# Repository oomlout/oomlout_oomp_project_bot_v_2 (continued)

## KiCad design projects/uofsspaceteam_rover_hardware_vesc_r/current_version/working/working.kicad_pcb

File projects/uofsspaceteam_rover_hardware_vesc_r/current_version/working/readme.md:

# rover_hardware
 
## summary 
* id: uofsspaceteam_rover_hardware_vesc_r
* user: uofsspaceteam
* name: rover_hardware
* board: vesc_r
* repo: https://github.com/UofSSpaceTeam/rover-hardware
* src_file_repo_kicad_pcb: Projects/Communication/VESC-R/VESC-R.kicad_pcb
* src_file_repo_kicad_pcb_link: https://github.com/UofSSpaceTeam/rover-hardware/tree/master/Projects/Communication/VESC-R/VESC-R.kicad_pcb
* src_file_repo_kicad_sch: Projects/Communication/VESC-R/CAN.kicad_sch
* src_file_repo_kicad_sch_link: https://github.com/UofSSpaceTeam/rover-hardware/tree/master/Projects/Communication/VESC-R/CAN.kicad_sch
* src_file_repo_brd: Projects/Communication/KiCad_USB/modified_eagle_files/RH025.1.brd
* src_file_repo_brd_link: https://github.com/UofSSpaceTeam/rover-hardware/tree/master/Projects/Communication/KiCad_USB/modified_eagle_files/RH025.1.brd
* src_file_repo_sch: Projects/Communication/KiCad_USB/RH025.1.sch
* src_file_repo_sch_link: https://github.com/UofSSpaceTeam/rover-hardware/tree/master/Projects/Communication/KiCad_USB/RH025.1.sch
* full details link: https://github.com/oomlout/oomlout_oomp_project_bot_v_2/tree/main/projects/uofsspaceteam_rover_hardware_vesc_r/current_version/working

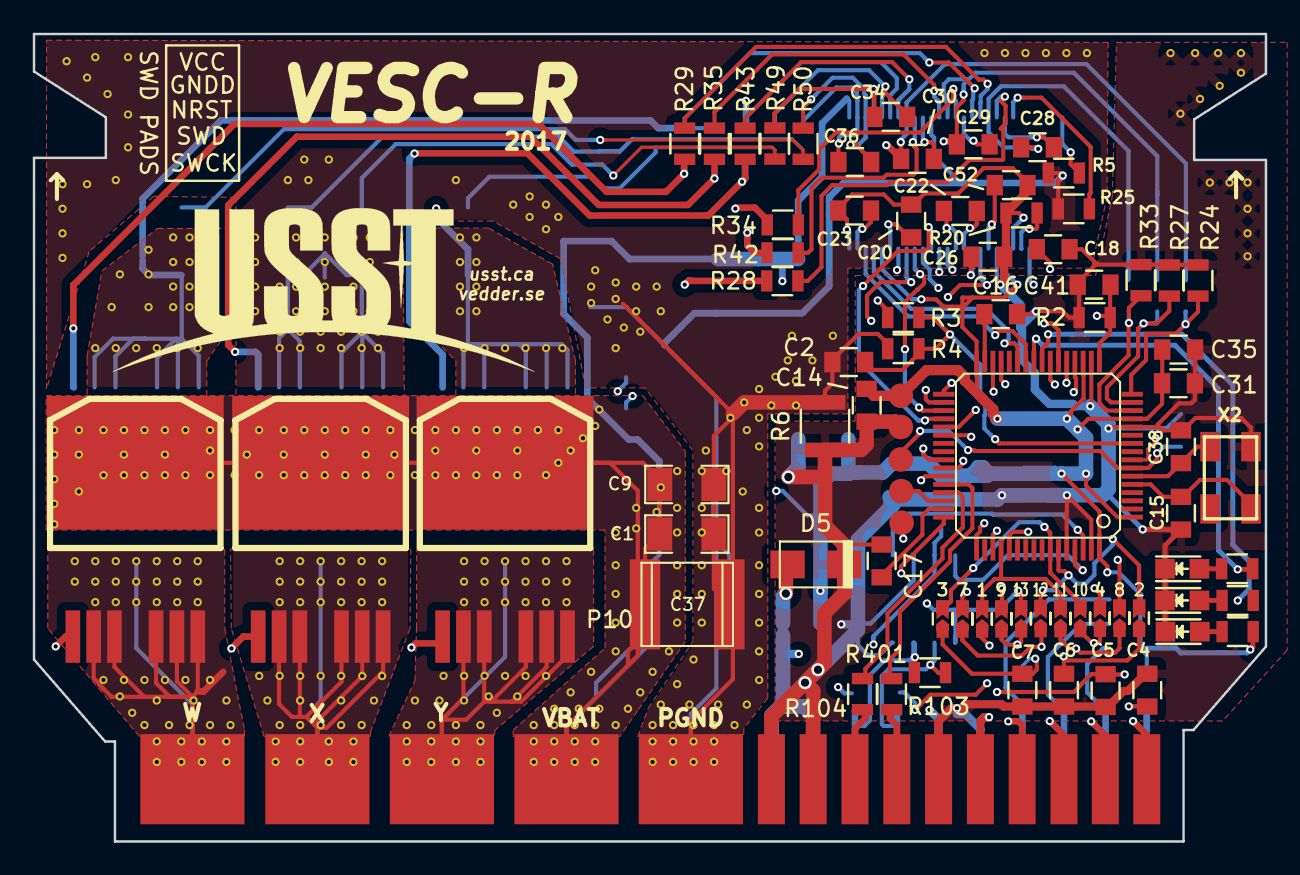
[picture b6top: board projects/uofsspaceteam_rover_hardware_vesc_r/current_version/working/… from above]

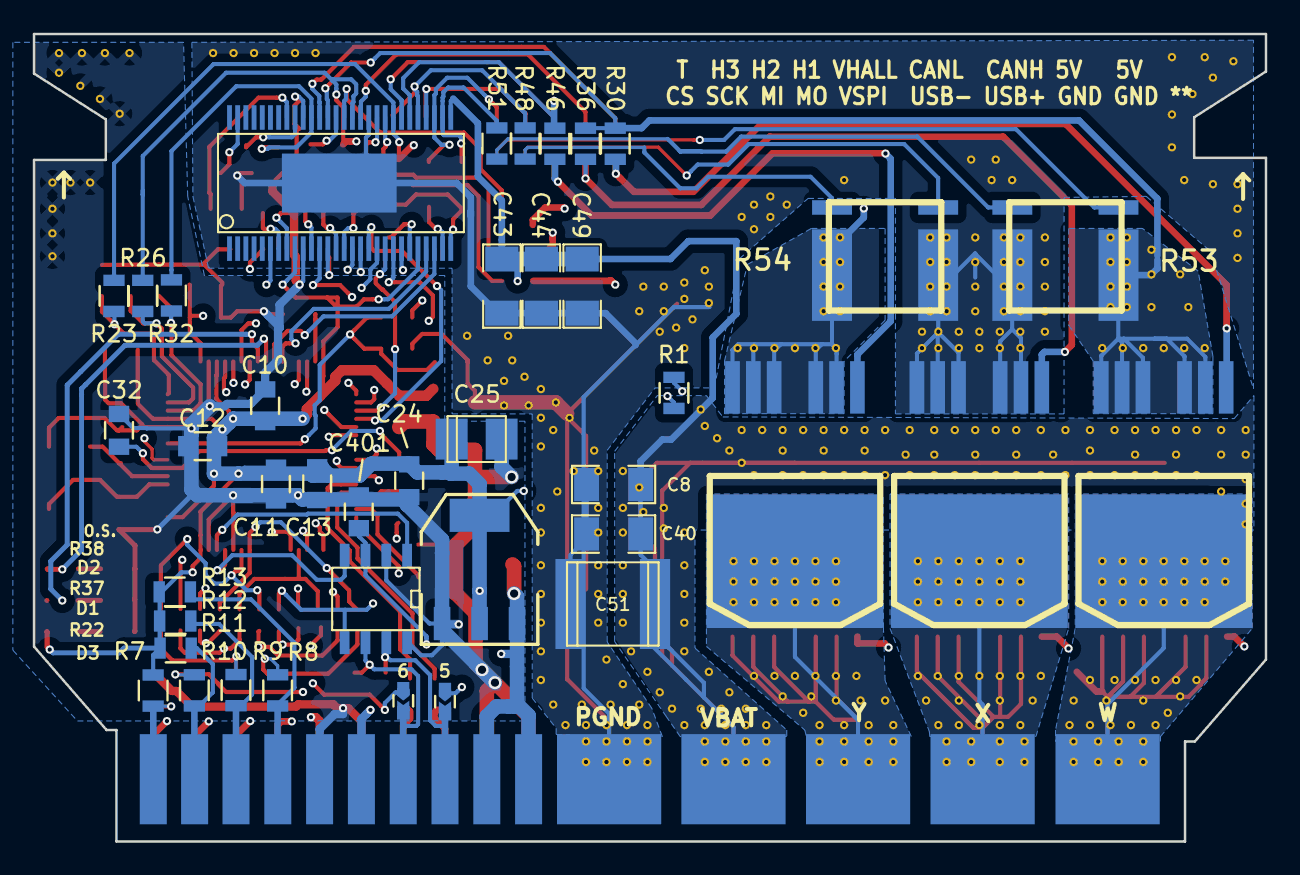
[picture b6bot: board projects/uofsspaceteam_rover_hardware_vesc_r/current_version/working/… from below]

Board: 4 copper layers, 75.2 x 49.3 mm, 117 parts (40 on the bottom side), 95 nets.

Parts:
1, 2, 3, 4, 5, 6, 7, 8, 9, 10, 11, 12, 13: Jumper_NC_Small; J_0603
C1, C8, C9, C40, C43, C44, C49: 10u,50V; SMD-1206
C2, C32: 100n; C_0805
C4, C5, C6, C7: 4n7; C_0805
C10, C11, C12, C13, C14, C16, C17, C18, C20, C23, C24, C26, C31, C35, C41, C52, C401: 2.2u; C_0805
C15, C38: 15p; C_0805
C22: 22n; C_0805
C25: 100u; c_tant_B
C28, C29, C30: 220n; C_0805
C34, C36: 2.2n; C_0805
C37: 15u,100V; c_2220
C51: 15u, 100v; c_2220
D1: GREEN; LED_0805
D2: RED; LED_0805
D3: LED; LED_0805
D5: TVS 5V; do214ac
GNDD: SWD_GND; Measurement_Point_Round-SMD-Pad_Small
NRST: NRST; Measurement_Point_Round-SMD-Pad_Small
P10: AMP17614426-2_EDGE; TE2007088-1_Edge_Long
Q1, Q2, Q3, Q4, Q5, Q6: IRFS7530; D2PAK-7-GDS
R1: NTC 10k; R_0805
R2, R7, R8, R9, R10, R20: 10k; R_0805
R3, R23, R26, R30, R32, R36, R46: 39k; R_0805
R4, R11, R12, R13, R22, R24, R27, R33: 2k2; R_0805
R5: 1k; R_0805
R6: 0; R_1210
R25: 1M; R_0805
R28, R29, R34, R35, R42, R43: 4R7; R_0805
R37, R38, R48, R49, R50, R51: 100R; R_0805
R53, R54: SHUNT; WSLP2726
R103, R104: 22R; R_0805
R401: NI; R_0805
SWCK: SWCLK; Measurement_Point_Round-SMD-Pad_Small
SWD: SWDIO; Measurement_Point_Round-SMD-Pad_Small
U1: STM32F40X_LQFP64; lqfp64_pad_mod
U2: TC2117; SOT-223
U3: DRV8302; TSSOP-56-PP
U401: MCP2562FD; SOIC-8-W
VCC: SWD_VCC; Measurement_Point_Round-SMD-Pad_Small
X2: CRYSTAL_GROUND_PIN; Crystal_5x3mm

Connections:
+5V: C401.1, D5.1, P10.6, P10.7, P10.10, U2.3, U401.3
/CAN bus transceiver/CAN_RX: U1.61, U401.4
/CAN bus transceiver/CAN_TX: U1.62, U401.1
/CAN_H: 5.2, P10.8, R401.1, U401.7
/CAN_L: 6.2, P10.9, R401.2, U401.6
/CS: 3.2, 10.2, U1.58
/CardEdge/CS: 4.1, 10.1, P10.16
/CardEdge/MISO: 7.1, 12.1, P10.18
/CardEdge/MOSI: 9.1, 13.1, P10.19
/CardEdge/SCK: 8.1, 11.1, P10.17
/Filters/HALL1_OUT: 3.1, C7.1, R8.2
/Filters/HALL2_OUT: 2.1, C6.1, R9.2
/Filters/HALL3_OUT: 1.1, C5.1, R10.2
/H1: P10.12, R8.1, R13.1
/H2: P10.13, R9.1, R12.1
/H3: P10.14, R10.1, R11.1
/MCU/ADC_TEMP: C41.1, R1.2, R2.1, U1.17
/MCU/AN_IN: C2.2, R3.2, R4.2, U1.10
/MCU/BR_SO1: U1.27, U3.25
/MCU/BR_SO2: U1.26, U3.26
/MCU/DC_CAL: U1.33, U3.12
/MCU/EN_GATE: U1.51, U3.16
/MCU/FAULT: U1.53, U3.6
/MCU/H1: U1.43, U3.17
/MCU/H2: U1.42, U3.19
/MCU/H3: U1.41, U3.21
/MCU/L1: U1.36, U3.18
/MCU/L2: U1.35, U3.20
/MCU/L3: U1.34, U3.22
/MCU/LED_GREEN: R37.2, U1.24
/MCU/LED_RED: R38.2, U1.25
/MCU/SENS1: R23.2, R24.2, U1.16
/MCU/SENS2: R26.2, R27.2, U1.15
/MCU/SENS3: R32.2, R33.2, U1.14
/MISO: 2.2, 12.2, U1.59
/MISO_2: 7.2, U1.22
/Mosfet driver/H1_LOW: Q2.S, R30.1, R36.1, R53.2, U3.44
/Mosfet driver/H3_LOW: Q6.S, R46.1, R54.1, U3.34
/Mosfet driver/M_H1: R28.2, U3.47
/Mosfet driver/M_H2: R34.2, U3.42
/Mosfet driver/M_H3: R42.2, U3.37
/Mosfet driver/M_L1: R29.2, U3.45
/Mosfet driver/M_L2: R35.2, U3.40
/Mosfet driver/M_L3: R43.2, U3.35
/Mosfet driver/SH1_A: R48.1, R54.3
/Mosfet driver/SH1_B: R49.1, R54.4
/Mosfet driver/SH2_A: R50.1, R53.4
/Mosfet driver/SH2_B: R51.1, R53.3
/RX_SCL_MOSI: 6.1, 9.2, U1.23, U1.29, U1.38
/SCK: 1.2, 11.2, U1.52
/SCK_2: 8.2, U1.21
/TX_SDA: 4.2, 5.1, U1.20, U1.30, U1.37
/Temp: C4.2, P10.15, R7.1, U1.8
/USBD_N: R103.1, U1.44
/USBD_P: R104.1, U1.45
/USB_N: P10.22, R103.2
/USB_P: P10.23, R104.2
/W: C28.1, P10.1, P10.30, Q1.S, Q2.D, R32.1, U3.46
/X: C29.1, P10.2, P10.29, Q3.S, Q4.D, R26.1, U3.41
/Y: C30.1, P10.3, P10.28, Q5.S, Q6.D, R23.1, U3.36
GND: C1.1, C2.1, C8.1, C9.1, C37.1, C40.1, C43.2, C44.2, C49.2, C51.1, P10.5, P10.26, Q4.S, R4.1, R5.1, R6.2, R25.1, R53.1, R54.2, U3.39, U3.57
GNDD: C4.1, C5.2, C6.2, C7.2, C10.1, C11.1, C12.1, C13.1, C14.1, C15.2, C16.2, C17.2, C18.2, C20.1, C23.1, C24.2, C25.2, C26.2, C31.1, C32.1, C35.1, C38.2, C41.2, C52.1, C401.2, D1.1, D2.1, D3.1, D5.2, GNDD.1, P10.11, P10.21, P10.24, P10.25, R2.2, R6.1, R20.2, R24.1, R27.1, R33.1, U1.12, U1.18, U1.60, U1.63, U2.1, U3.8, U3.10, U3.28, U401.2, U401.8, X2.3
NRST: C32.2, NRST.1, U1.7
unnamed: C15.1, U1.5, X2.1
unnamed: C16.1, U1.31
unnamed: C17.1, U1.47
unnamed: C18.1, C26.1, U3.13
unnamed: C20.2, C52.2, U3.11, U3.23
unnamed: C22.1, U3.14
unnamed: C22.2, U3.15
unnamed: C23.2, U3.27
unnamed: C28.2, U3.48
unnamed: C29.2, U3.43
unnamed: C30.2, U3.38
unnamed: C34.1, R48.2, U3.33
unnamed: C34.2, R49.2, U3.32
unnamed: C36.1, R50.2, U3.31
unnamed: C36.2, R51.2, U3.30
unnamed: C38.1, U1.6, X2.2
unnamed: D1.2, R37.1
unnamed: D2.2, R38.1
unnamed: D3.2, R22.1
unnamed: Q1.G, R28.1
unnamed: Q2.G, R29.1, R30.2
unnamed: Q3.G, R34.1
unnamed: Q4.G, R35.1, R36.2
unnamed: Q5.G, R42.1
unnamed: Q6.G, R43.1, R46.2
unnamed: R5.2, U3.55
unnamed: R20.1, U3.7
unnamed: R25.2, U3.49
SWCLK: SWCK.1, U1.49
SWDIO: SWD.1, U1.46
VCC: 13.2, C10.2, C11.2, C12.2, C13.2, C14.2, C24.1, C25.1, C31.2, C35.2, P10.20, R1.1, R7.2, R11.2, R12.2, R13.2, R22.2, U1.1, U1.13, U1.19, U1.32, U1.48, U1.64, U2.2, U3.9, U3.24, U401.5, VCC.1
V_SUPPLY: C1.2, C8.2, C9.2, C37.2, C40.2, C43.1, C44.1, C49.1, C51.2, P10.4, P10.27, Q1.D, Q3.D, Q5.D, R3.1, U3.29
